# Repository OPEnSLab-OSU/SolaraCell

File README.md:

Project Creator: Aiden Olsen

The purpose of the SolaraCell is simple, provide solar lipo charging without needing to arrange
the components on the end PCB yourself. The SolaraCell uses the BQ24074 smart charging IC allowing
you to power your projects.

<!-- More information about assembly, testing, and operation can be found at the wiki. -->

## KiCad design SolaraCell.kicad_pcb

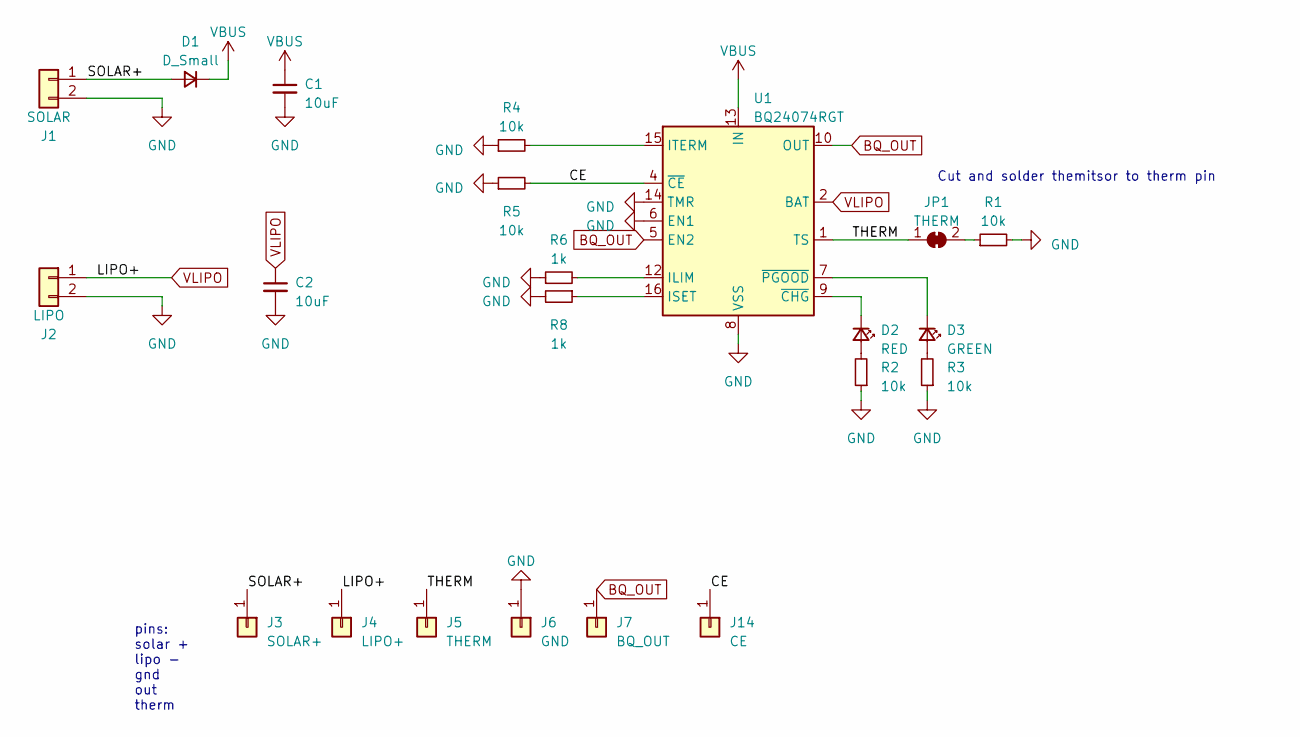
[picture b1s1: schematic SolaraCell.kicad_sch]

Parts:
C1, C2: 10uF; C_0805_2012Metric
D1: D_Small; D_SOD-123
D2: RED; LED_0805_2012Metric
D3: GREEN; LED_0805_2012Metric
J1: SOLAR; TerminalBlock_TE_282834-2_1x02_P2.54mm_Horizontal
J2: LIPO; JST_PH_S2B-PH-SM4-TB_1x02-1MP_P2.00mm_Horizontal
J3: SOLAR+; PCBWay_CastellatedHole
J4: LIPO+; PCBWay_CastellatedHole
J5: THERM; PCBWay_CastellatedHole
J6: GND; PCBWay_CastellatedHole
J7: BQ_OUT; PCBWay_CastellatedHole
J14: CE; PCBWay_CastellatedHole
JP1: THERM; SolderJumper-2_P1.3mm_Bridged_RoundedPad1.0x1.5mm
R1, R2, R3, R4, R5: 10k; R_0805_2012Metric
R6, R8: 1k; R_0805_2012Metric
U1: BQ24074RGT; VQFN-16-1EP_3x3mm_P0.5mm_EP1.6x1.6mm

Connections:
/CE: J14.1, R5.2, U1.4 (~CE)
/SOLAR+: D1.2 (A), J1.1, J3.1
/THERM: J5.1, JP1.1 (A), U1.1 (TS)
BQ_OUT: J7.1, U1.5 (EN2), U1.10 (OUT), U1.11 (OUT)
GND: C1.2, C2.2, J1.2, J2.2, J6.1, R1.2, R2.1, R3.1, R4.1, R5.1, R6.1, R8.2, U1.6 (EN1), U1.8 (VSS), U1.14 (TMR), U1.17 (VSS)
unnamed: D2.2 (A), R2.2
unnamed: D2.1 (K), U1.9 (~CHG)
unnamed: D3.2 (A), R3.2
unnamed: D3.1 (K), U1.7 (~PGOOD)
unnamed: JP1.2 (B), R1.1
unnamed: R6.2, U1.12 (ILIM)
unnamed: R8.1, U1.16 (ISET)
unnamed: R4.2, U1.15 (ITERM)
VBUS: C1.1, D1.1 (K), U1.13 (IN)
VLIPO: C2.1, J2.1, J4.1, U1.2 (BAT), U1.3 (BAT)

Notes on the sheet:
pins: solar + lipo - gnd out therm
Cut and solder themitsor to therm pin

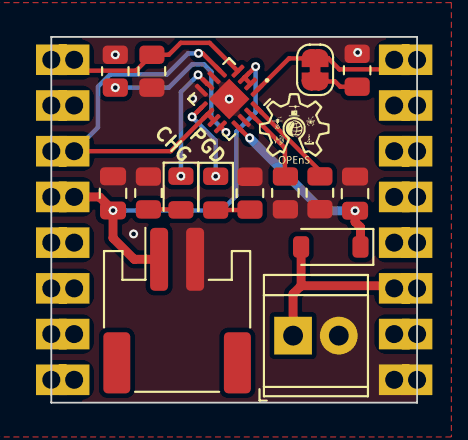
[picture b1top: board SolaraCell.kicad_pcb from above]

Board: 2 copper layers, 20.3 x 20.3 mm, 22 parts (0 on the bottom side), 15 nets.

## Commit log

2023-06-05 init
2023-06-05 basic info
